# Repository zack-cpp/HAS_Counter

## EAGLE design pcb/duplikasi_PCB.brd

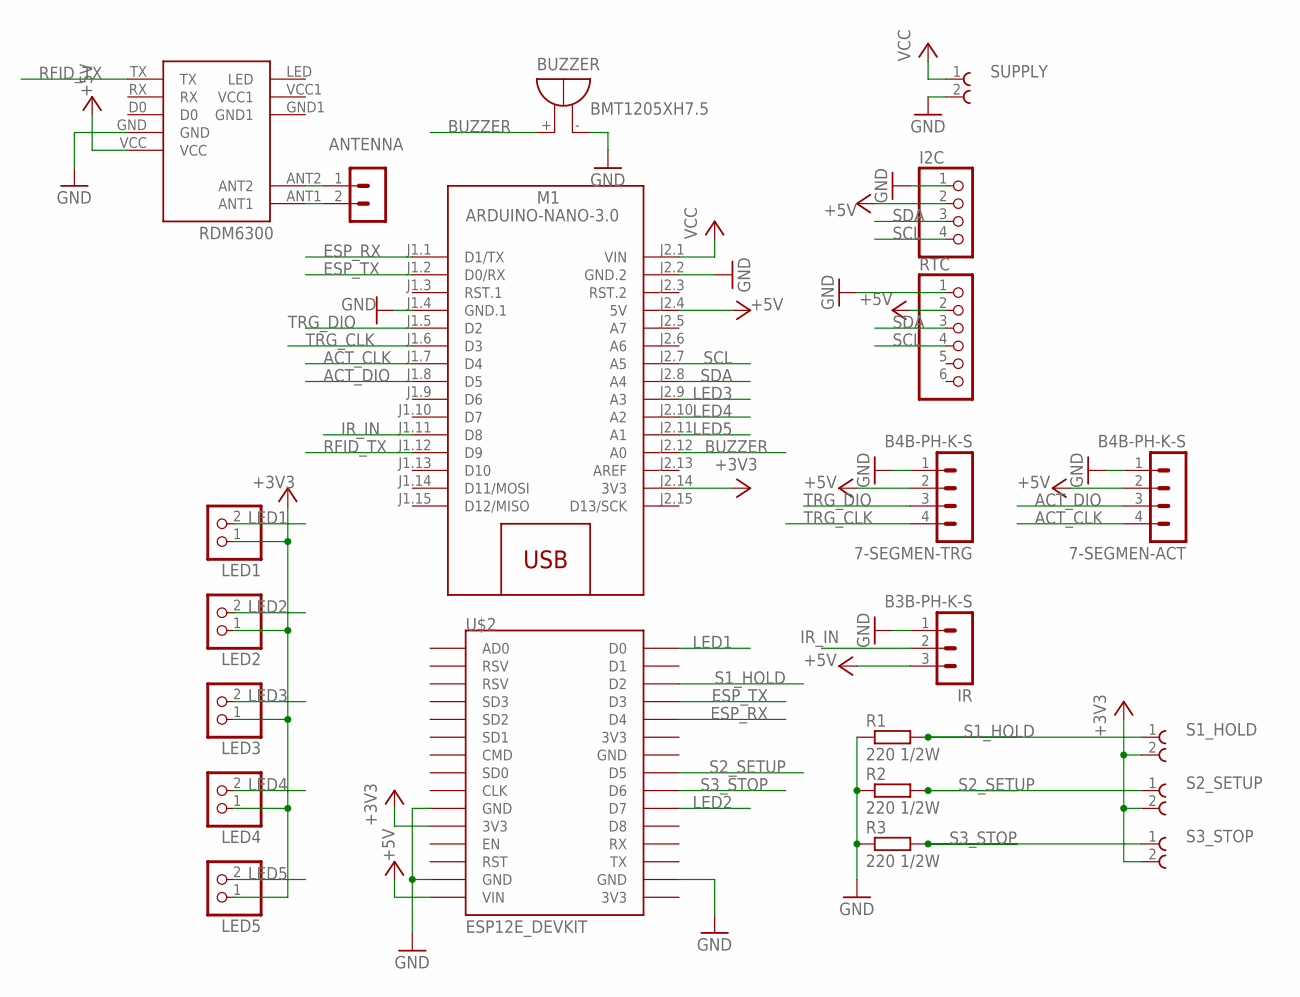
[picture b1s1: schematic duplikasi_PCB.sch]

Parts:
7-SEGMEN-ACT, 7-SEGMEN-TRG: B4B-PH-K-S
ANTENNA: B2B-PH-K-S
BUZZER: BMT1205XH7.5
I2C: PINHD-1X4; 1X04
IR: B3B-PH-K-S
LED1, LED2, LED3, LED4, LED5: PINHD-1X2; 1X02
M1: ARDUINO-NANO-3.0
R1, R2, R3: 220 1/2W; 0207/10
RDM1: RDM6300
RTC: PINHD-1X6; 1X06
S1_HOLD, S2_SETUP, S3_STOP: 691101710002
SUPPLY: 691101710002
U$2: ESP12E_DEVKIT

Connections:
+3V3: LED1.1, LED2.1, LED3.1, LED4.1, LED5.1, M1.J2.14 (3V3), S1_HOLD.2, S2_SETUP.2, S3_STOP.2, U$2.3V3@0 (3V3)
+5V: 7-SEGMEN-ACT.2, 7-SEGMEN-TRG.2, I2C.2, IR.3, M1.J2.4 (5V), RDM1.VCC, RTC.2, U$2.VIN
ACT_CLK: 7-SEGMEN-ACT.4, M1.J1.7 (D4)
ACT_DIO: 7-SEGMEN-ACT.3, M1.J1.8 (D5)
BUZZER: BUZZER.+, M1.J2.12 (A0)
ESP_RX: M1.J1.1 (D1/TX), U$2.D4
ESP_TX: M1.J1.2 (D0/RX), U$2.D3
GND: 7-SEGMEN-ACT.1, 7-SEGMEN-TRG.1, BUZZER.-, I2C.1, IR.1, M1.J1.4 (GND.1), M1.J2.2 (GND.2), R1.1, R2.1, R3.1, RDM1.GND, RTC.1, SUPPLY.2, U$2.GND@0 (GND), U$2.GND@1 (GND), U$2.GND@3 (GND)
IR_IN: IR.2, M1.J1.11 (D8)
LED1: LED1.2, U$2.D0
LED2: LED2.2, U$2.D7
LED3: LED3.2, M1.J2.9 (A3)
LED4: LED4.2, M1.J2.10 (A2)
LED5: LED5.2, M1.J2.11 (A1)
unnamed: ANTENNA.1, RDM1.ANT2
unnamed: ANTENNA.2, RDM1.ANT1
RFID_TX: M1.J1.12 (D9), RDM1.TX
S1_HOLD: R1.2, S1_HOLD.1, U$2.D2
S2_SETUP: R2.2, S2_SETUP.1, U$2.D5
S3_STOP: R3.2, S3_STOP.1, U$2.D6
SCL: I2C.4, M1.J2.7 (A5), RTC.4
SDA: I2C.3, M1.J2.8 (A4), RTC.3
TRG_CLK: 7-SEGMEN-TRG.4, M1.J1.6 (D3)
TRG_DIO: 7-SEGMEN-TRG.3, M1.J1.5 (D2)
VCC: M1.J2.1 (VIN), SUPPLY.1

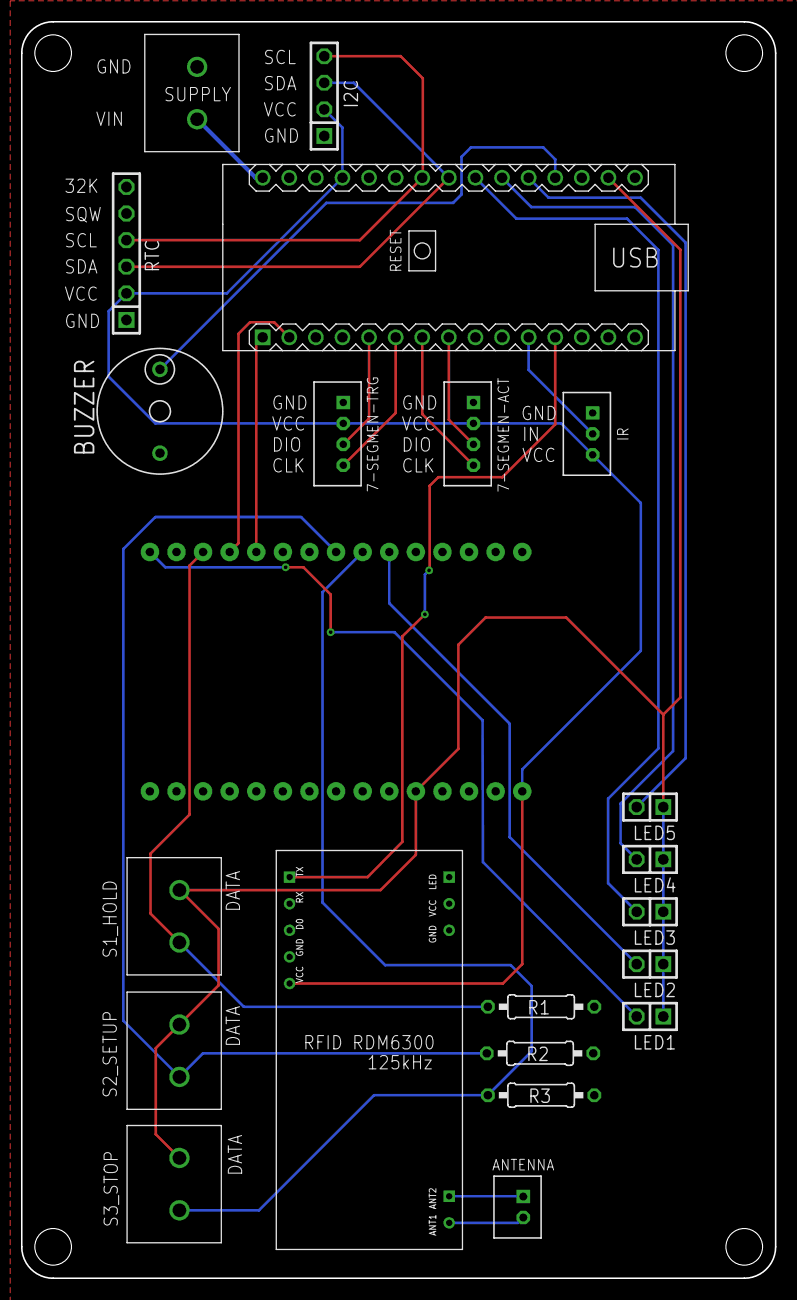
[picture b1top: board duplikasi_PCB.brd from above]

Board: 2 copper layers, 72.0 x 120.0 mm, 22 parts (0 on the bottom side), 25 nets.

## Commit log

2021-03-21 libraries for HAS counter
2021-03-21 EAGLE PCB design
2021-03-21 firmware for nano
2021-03-21 firmware for ESP
2021-03-21 folder replace
2021-03-29 Add button HOLD, SETUP, STOP
2021-03-29 Handle button command from ESP
2021-03-29 Adjust some copper wire position
2021-04-02 Integrasi dasar dengan andon
2021-04-05 Remove unused code
2021-04-05 Add button handle and buzzer output
2021-04-05 Changing I2C LCD library
2021-04-08 remove pin setup
2021-04-08 Add WiFi manager feature
2021-04-16 Add wifi manager
2021-04-16 Handle wifi manager from esp
2021-04-19 Auto connect server and wifi manager
2021-04-19 Handle auto connect server and wifi manager
2021-05-01 fix rtc bug from last version
2021-05-10 fix button led bug
2021-05-13 include libraries
2021-05-13 add NTP for RTC and improve communication
2021-05-13 add NTP handler and improve communication
2021-05-13 remove PCB files
2021-06-28 add maintenance without check
2021-07-01 Improve sensor reading with interrupt
2021-07-02 Update web UI for MQTT server input

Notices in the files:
parts and their libraries:
diy-modules: Released under the Creative Commons Attribution 4.0 International License: http://creativecommons.org/licenses/by/4.0
Terminal Block 5mm: Copyright: Würth Elektronik
